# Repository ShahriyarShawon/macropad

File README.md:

# Pi Pico Based Macropad project

## Footprints
    - RPiPico in MacropadFootprints

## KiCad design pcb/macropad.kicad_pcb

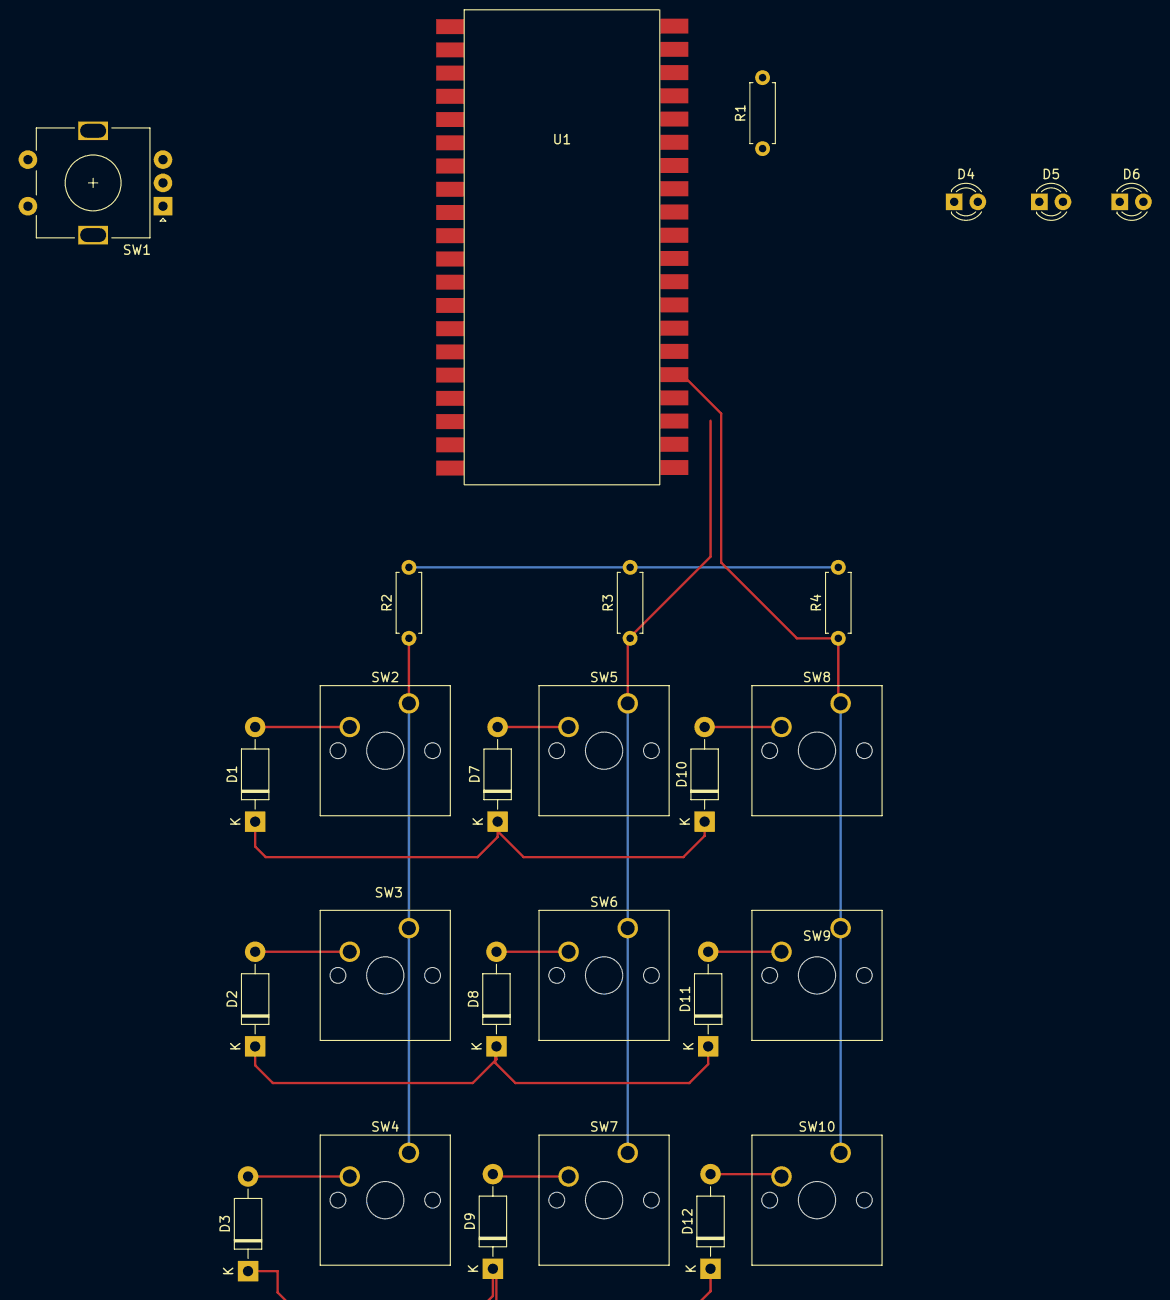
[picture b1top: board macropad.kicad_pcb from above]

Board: 2 copper layers, 27 parts (0 on the bottom side), 25 nets.

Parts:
D1, D2, D3, D7, D8, D9, D10, D11, D12: 1N4007; D_DO-41_SOD81_P10.16mm_Horizontal
D4, D5, D6: LED; LED_D3.0mm
R1, R2, R3, R4: R; R_Axial_DIN0207_L6.3mm_D2.5mm_P7.62mm_Horizontal
SW1: RotaryEncoder_Switch; RotaryEncoder_Alps_EC11E-Switch_Vertical_H20mm
SW2, SW3, SW4, SW5, SW6, SW7, SW8, SW9, SW10: SW_Push; SW_Cherry_MX_1.00u_PCB
U1: PICO_RP2040; RPiPico

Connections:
/Pin 15: D1.1 (K), D7.1 (K), D10.1 (K), U1.15 (GP11)
/Pin 16: D2.1 (K), D8.1 (K), D11.1 (K), U1.16 (GP12)
/Pin 17: D3.1 (K), D9.1 (K), D12.1 (K), U1.17 (GP13)
GND: R1.2, R2.2, R3.2, R4.2
unnamed: D1.2 (A), SW2.2
unnamed: D2.2 (A), SW3.2
unnamed: D3.2 (A), SW4.2
unnamed: D4.1 (K), U1.34 (GP28)
unnamed: D4.2 (A), D5.2 (A), D6.2 (A)
unnamed: D5.1 (K), U1.32 (GP27)
unnamed: D6.1 (K), U1.31 (GP26)
unnamed: D7.2 (A), SW5.2
unnamed: D8.2 (A), SW6.2
unnamed: D9.2 (A), SW7.2
unnamed: D10.2 (A), SW8.2
unnamed: D11.2 (A), SW9.2
unnamed: D12.2 (A), SW10.2
unnamed: R2.1, SW2.1, SW3.1, SW4.1, U1.27 (GP21)
unnamed: R3.1, SW5.1, SW6.1, SW7.1, U1.26 (GP20)
unnamed: R4.1, SW8.1, SW9.1, SW10.1, U1.25 (GP19)
unnamed: SW1.A, U1.9 (GP6)
unnamed: SW1.B, U1.7 (GP5)
unnamed: SW1.C, U1.8 (GND)
unnamed: SW1.S1, U1.11 (GP8)
unnamed: SW1.S2, U1.3 (GND)

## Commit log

2022-01-25 Added readme and pdf of pi pico mechanical specifications
2022-01-25 Placed all pins for pico
2022-02-04 Corrected footprints for resistors
2022-03-10 Finished pcb layout
2022-03-13 First Possible release
2022-03-13 Added leds and connected switch from rotary encoder
